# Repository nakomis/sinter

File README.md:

# Sinter — Combining hardware in cruel and unusual ways

## Support

If you find this useful, please consider buying me a coffee:

## Table of Contents

<!-- toc -->

- [Overview](#overview)
- [Architecture Diagram](#architecture-diagram)
- [Repository Layout](#repository-layout)
- [GA-M68MT-S2 Board Architecture](#ga-m68mt-s2-board-architecture)
- [Hardware](#hardware)
- [Architecture Diagrams](#architecture-diagrams)
- [Support](#support)

<!-- tocstop -->

## Overview

Sinter is an agentic compute rig built around a Phenom II X4 965 (AM3) as the execution engine, a Tang Primer 20K FPGA as the memory and bus bridge, and an ESP32 as the orchestration layer.

The ESP32 accepts natural-language problem descriptions, sends them to a local LLM (via Ollama), receives Forth code in response, compiles it to x86-64, injects the binary into the Phenom II's DDR3 via the FPGA/PCIe bridge, executes it, validates the result, and iterates on failure.

> ⭐⭐⭐⭐⭐ — *"Delightfully unhinged in exactly the right way"* — [Copilot](docs/notes/research/sinter-project-assessment-copilot.md)
>
> ⭐⭐⭐⭐⭐ — *"Slow, uncached, synchronization hell"* — [ChatGPT](docs/notes/research/sinter-project-assessment-chatgpt.md#direct-execution-from-bar)
>
> ⭐⭐⭐⭐⭐ — *"Ambitious and cool, but genuinely tricky"* — [Grok](docs/notes/research/sinter-project-assessment-grok.md#3-pci-bar-execute-in-place-architecture--high-risk-many-pitfalls)
>
> ⭐⭐⭐⭐⭐ — *"A desk of whirring salvage spending three days to say 'Hello'"* — Claude

## Architecture Diagram

## Repository Layout

```
sinter/
  embedded/
    esp32/      # ESP32 firmware: agentic loop, Forth-to-x86-64 compiler, orchestration
    fpga/       # HDL for Tang Primer 20K: DDR3 bridge, PCIe endpoint, SATA controller
    phenom/     # Bare-metal x86: bootloader, kernel modules, MSR tooling
  forth/        # Forth-to-x86-64 compiler: portable C11 library, host tests (SINT-25)
  docs/
    architecture/   # draw.io source and generated SVGs
```

## GA-M68MT-S2 Board Architecture

For reference, the textbook early-2000s Intel desktop block diagram looks like
this:

CPU on a front-side bus to a **northbridge** (MCH) that owns RAM and AGP/PCIe×16,
then a **southbridge** (ICH) hanging off it that fans out to PCI, USB, SATA/IDE,
audio, LAN, Super I/O (PS/2, serial, parallel, floppy) and the BIOS flash. Fast
stuff close to the CPU, slow/legacy stuff one hop further out.

The Sinter host board (Gigabyte GA-M68MT-S2, Phenom II AM3, nForce 630a /
GeForce 7025) is **not** that picture. It differs in three important ways:

1. **RAM doesn't go through the chipset.** AM3 CPUs have the DDR3 memory
   controller **on-die**. The DIMM slots connect straight to the CPU.
2. **No FSB — it's HyperTransport.** The CPU↔chipset link is a HyperTransport
   3.0 point-to-point bus.
3. **No separate north/southbridge — it's one chip.** The nForce 630a / MCP68
   is a single-chip chipset: PCIe root, the integrated GeForce 7025 iGPU (the
   VGA output), PCI, USB, SATA, LAN MAC, HD Audio, LPC and the SPI master all
   in one package.

Two project-specific extras the generic diagram doesn't show:

- **BIOS is SPI, not LPC.** The MX25L1605E talks SPI to the chipset's SPI
  master — which is why a serprog rig works at all.
- **DualBIOS.** There are **two** flash chips on that SPI bus plus a small
  selector (the "DualBIOS controller").

## Hardware

| Component | Role |
|---|---|
| Phenom II X4 965 (AM3 / GA-M68MT-S2) | x86-64 execution engine |
| Tang Primer 20K FPGA + DDR3 SO-DIMM | Memory bridge, PCIe endpoint, SATA/SPI controller |
| ESP32 | Orchestration, Forth compiler, Ollama client |
| ESP32-S3-CAM | Vision input for inference tasks |

## Architecture Diagrams

`docs/architecture/sinter.drawio` is the source for the diagram above.
The SVG is auto-regenerated on commit by the pre-commit hook in `.githooks/pre-commit`.

To activate the hook after cloning:

```bash
git config core.hooksPath .githooks
```

## Support

If you find this useful, please consider buying me a coffee:

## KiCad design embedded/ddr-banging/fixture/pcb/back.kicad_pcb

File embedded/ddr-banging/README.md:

# DDR-banging (SINT-100)

Driving a desktop DDR3 DIMM directly from an RP2350B, so that an ESP32 can have
gigabytes of RAM. Plane epic: **SINT-100**.

| Path | What |
|---|---|
| `RUNBOOK.md` | Bring-up, step by step: parcel to first burst, with what "good" looks like at each step |
| `EXECUTOR.md` | Design note for the PIO executor (milestone 11): SM layout, word streams, timing, draft programs |
| `firmware/` | RP2350B bring-up firmware: shell, DLL-off DDR3 sequences, ESP32 link (slave) |
| `proto/` | `ddrlink`: the ESP32 ↔ RP2350B SPI protocol, shared by both sides |
| `esp32-client/` | ESP-IDF component `ddrbang` (the ESP32's API to the DIMM) and the 128 MB write/verify test |
| `pogo-pins.md` | Which DIMM pads the fixture contacts, and what each carries |
| `fixture/dimm-pogo-fixture.scad` | Resin pogo-pin fixture (Elegoo Mars 5 Ultra): two jaws, floor, end stops, notch key, hole test strip, insertion gauge |
| `fixture/pcb/gen_pcb.py` | Generates the two breakout PCBs (KiCad) from the `.scad`'s numbers |
| `fixture/pcb/art/` | Silkscreen cats: Tau (front board), Kappa (back board) |

## Rebuilding

```sh
# STLs
openscad -D 'part="front"' -o fixture/stl/front.stl fixture/dimm-pogo-fixture.scad   # also back | test | gauge

# PCBs, DRC, Gerbers for JLCPCB
cd fixture/pcb
python3 gen_pcb.py
kicad-cli pcb drc front.kicad_pcb        # and back
kicad-cli pcb export gerbers --layers F.Cu,B.Cu,F.Mask,B.Mask,F.SilkS,B.SilkS,Edge.Cuts --no-x2 --subtract-soldermask -o gerbers-front/ front.kicad_pcb
kicad-cli pcb export drill --format excellon --excellon-separate-th -o gerbers-front/ front.kicad_pcb
```

Change geometry in the `.scad` only; the PCB generator parses pin lists, pad
positions and bolt positions from it, so the jaw and the boards cannot disagree.

## Key numbers

- Test stick: Samsung M391B5673FH0-CH9 (2 GB 2Rx8 ECC UDIMM, K4B1G0846F chips).
- Gold fingers 2.4 mm tall (measured); pin rows at 0.75 and 2.03 mm above the edge.
- P75-B1 pogo pins; 1.15 mm plated holes (JLCPCB PTH tolerance +0.13/−0.08).
- Four M3×25 bolts clamp PCB–jaw–floor–jaw–PCB.
- PCBs ordered from JLCPCB 2026-10-10: 1.6 mm, front black, back white.

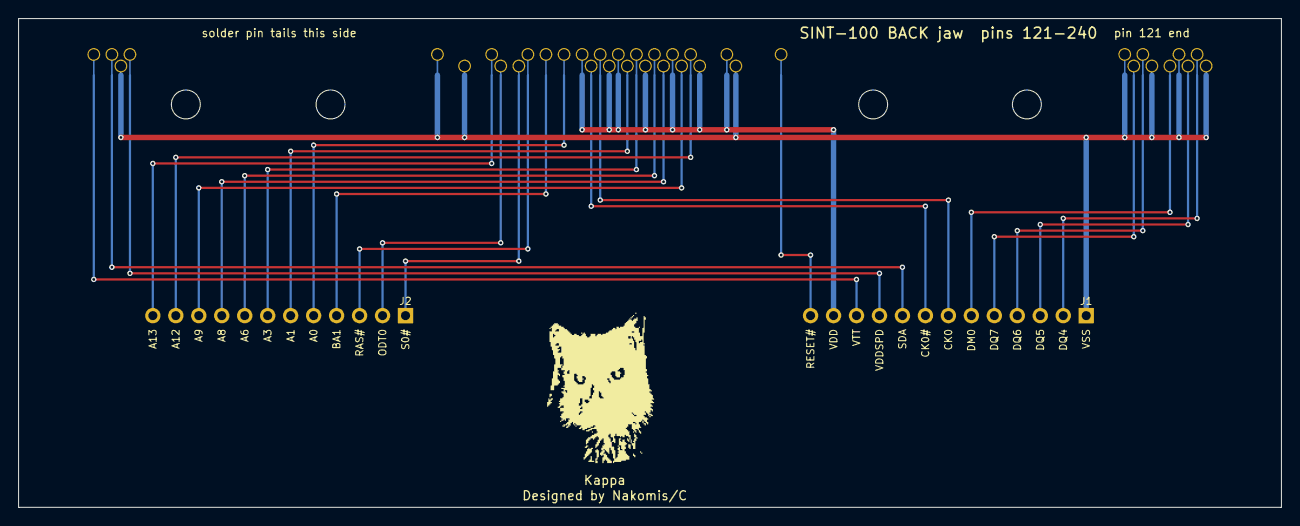
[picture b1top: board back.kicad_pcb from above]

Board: 2 copper layers, 139.7 x 54.0 mm, 45 parts (0 on the bottom side), 25 nets.

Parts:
ART2: Kappa; ART_KAPPA
H1, H2, H3, H4: M3
J1: HDR_1x13
J2: HDR_1x12
P121, P124, P127, P130, P169, P199, P202, P237: VSS; POGO_P75
P122: DQ4; POGO_P75
P123: DQ5; POGO_P75
P125: DM0; POGO_P75
P128: DQ6; POGO_P75
P129: DQ7; POGO_P75
P168: RESET#; POGO_P75
P170, P173, P176, P179, P182, P183, P186: VDD; POGO_P75
P174: A12; POGO_P75
P175: A9; POGO_P75
P177: A8; POGO_P75
P178: A6; POGO_P75
P180: A3; POGO_P75
P181: A1; POGO_P75
P184: CK0; POGO_P75
P185: CK0#; POGO_P75
P188: A0; POGO_P75
P190: BA1; POGO_P75
P192: RAS#; POGO_P75
P193: S0#; POGO_P75
P195: ODT0; POGO_P75
P196: A13; POGO_P75
P236: VDDSPD; POGO_P75
P238: SDA; POGO_P75
P240: VTT; POGO_P75

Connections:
A0: J2.5, P188.1
A1: J2.6, P181.1
A3: J2.7, P180.1
A6: J2.8, P178.1
A8: J2.9, P177.1
A9: J2.10, P175.1
A12: J2.11, P174.1
A13: J2.12, P196.1
BA1: J2.4, P190.1
CK0: J1.7, P184.1
CK0#: J1.8, P185.1
DM0: J1.6, P125.1
DQ4: J1.2, P122.1
DQ5: J1.3, P123.1
DQ6: J1.4, P128.1
DQ7: J1.5, P129.1
ODT0: J2.2, P195.1
RAS#: J2.3, P192.1
RESET#: J1.13, P168.1
S0#: J2.1, P193.1
SDA: J1.9, P238.1
VDD: J1.12, P170.1, P173.1, P176.1, P179.1, P182.1, P183.1, P186.1
VDDSPD: J1.10, P236.1
VSS: J1.1, P121.1, P124.1, P127.1, P130.1, P169.1, P199.1, P202.1, P237.1
VTT: J1.11, P240.1

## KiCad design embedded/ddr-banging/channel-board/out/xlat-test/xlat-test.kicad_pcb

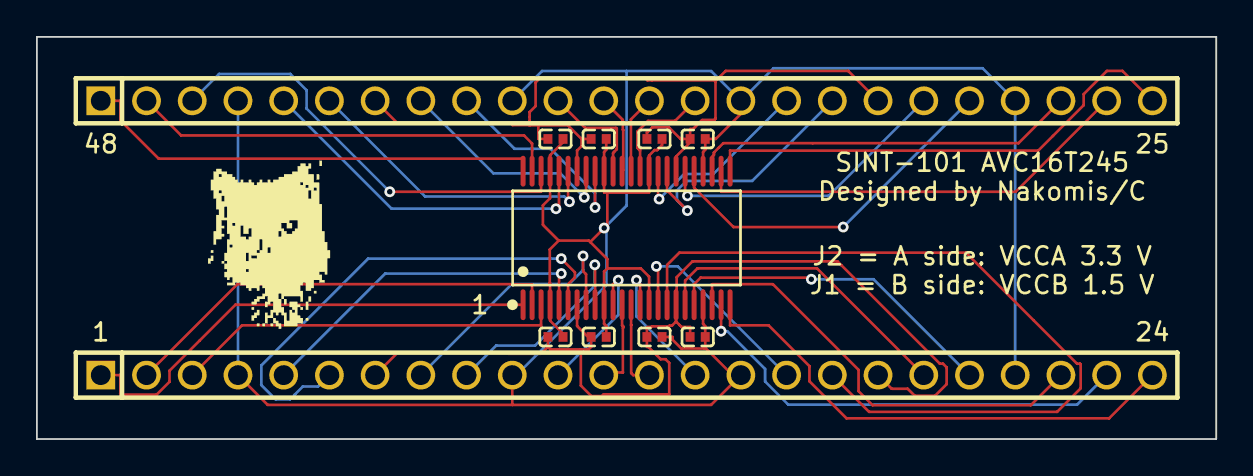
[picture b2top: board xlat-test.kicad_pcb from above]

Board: 2 copper layers, 65.5 x 22.3 mm, 12 parts (0 on the bottom side), 39 nets.

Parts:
ART: ART
C1, C3, C5, C7: 100nF; C0402
C2, C4, C6, C8: 1uF; C0402
J1, J2: 1x24 header; HDR-TH_24P-P2.54-V-M
U1: SN74AVC16T245DGGR; TSSOP-48_L12.6-W6.2-P0.50-LS8.1-BL

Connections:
1A1: J2.2, U1.47
1A2: J2.3, U1.46
1A3: J2.5, U1.44
1A4: J2.6, U1.43
1A5: J2.8, U1.41
1A6: J2.9, U1.40
1A7: J2.11, U1.38
1A8: J2.12, U1.37
1B1: J1.2, U1.2
1B2: J1.3, U1.3
1B3: J1.5, U1.5
1B4: J1.6, U1.6
1B5: J1.8, U1.8
1B6: J1.9, U1.9
1B7: J1.11, U1.11
1B8: J1.12, U1.12
1DIR: J1.1, U1.1
1OE#: J2.1, U1.48
2A1: J2.13, U1.36
2A2: J2.14, U1.35
2A3: J2.16, U1.33
2A4: J2.17, U1.32
2A5: J2.19, U1.30
2A6: J2.20, U1.29
2A7: J2.22, U1.27
2A8: J2.23, U1.26
2B1: J1.13, U1.13
2B2: J1.14, U1.14
2B3: J1.16, U1.16
2B4: J1.17, U1.17
2B5: J1.19, U1.19
2B6: J1.20, U1.20
2B7: J1.22, U1.22
2B8: J1.23, U1.23
2DIR: J1.24, U1.24
2OE#: J2.24, U1.25
GND: C1.2, C2.2, C3.2, C4.2, C5.2, C6.2, C7.2, C8.2, J1.4, J1.10, J1.15, J1.21, J2.4, J2.10, J2.15, J2.21, U1.4, U1.10, U1.15, U1.21, U1.28, U1.34, U1.39, U1.45
VCCA: C1.1, C2.1, C3.1, C4.1, J2.7, J2.18, U1.31, U1.42
VCCB: C5.1, C6.1, C7.1, C8.1, J1.7, J1.18, U1.7, U1.18

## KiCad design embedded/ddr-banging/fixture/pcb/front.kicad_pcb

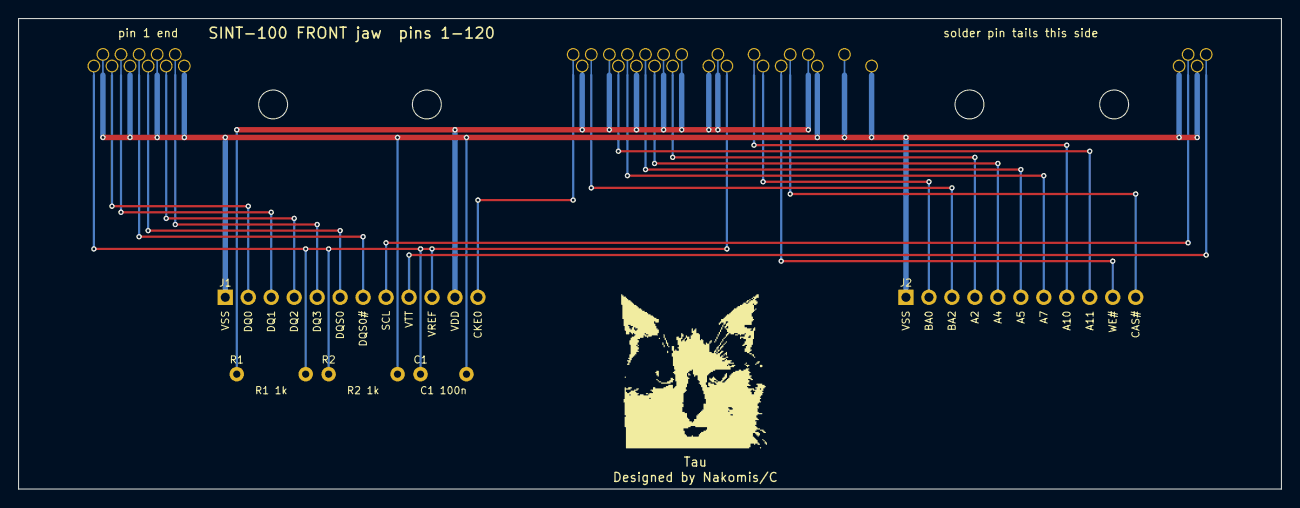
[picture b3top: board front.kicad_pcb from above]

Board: 2 copper layers, 139.7 x 52.0 mm, 48 parts (0 on the bottom side), 22 nets.

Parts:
ART1: Tau; ART_TAU
C1: 100n; CAP_THT
H1, H2, H3, H4: M3
J1: HDR_1x12
J2: HDR_1x11
P1, P67: VREF; POGO_P75
P2, P5, P8, P11, P77, P80, P83, P117, P119: VSS; POGO_P75
P3: DQ0; POGO_P75
P4: DQ1; POGO_P75
P6: DQS0#; POGO_P75
P7: DQS0; POGO_P75
P9: DQ2; POGO_P75
P10: DQ3; POGO_P75
P50: CKE0; POGO_P75
P51, P54, P57, P60, P62, P65, P66, P76: VDD; POGO_P75
P52: BA2; POGO_P75
P55: A11; POGO_P75
P56: A7; POGO_P75
P58: A5; POGO_P75
P59: A4; POGO_P75
P61: A2; POGO_P75
P70: A10; POGO_P75
P71: BA0; POGO_P75
P73: WE#; POGO_P75
P74: CAS#; POGO_P75
P118: SCL; POGO_P75
P120: VTT; POGO_P75
R1, R2: 1k; AXIAL

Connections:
A2: J2.4, P61.1
A4: J2.5, P59.1
A5: J2.6, P58.1
A7: J2.7, P56.1
A10: J2.8, P70.1
A11: J2.9, P55.1
BA0: J2.2, P71.1
BA2: J2.3, P52.1
CAS#: J2.11, P74.1
CKE0: J1.12, P50.1
DQ0: J1.2, P3.1
DQ1: J1.3, P4.1
DQ2: J1.4, P9.1
DQ3: J1.5, P10.1
DQS0: J1.6, P7.1
DQS0#: J1.7, P6.1
SCL: J1.8, P118.1
VDD: J1.11, P51.1, P54.1, P57.1, P60.1, P62.1, P65.1, P66.1, P76.1, R1.1
VREF: C1.1, J1.10, P1.1, P67.1, R1.2, R2.1
VSS: C1.2, J1.1, J2.1, P2.1, P5.1, P8.1, P11.1, P77.1, P80.1, P83.1, P117.1, P119.1, R2.2
VTT: J1.9, P120.1
WE#: J2.10, P73.1

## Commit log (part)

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2026-05-03 chore: scaffold sinter with standard project layout
2026-05-03 chore(docs): replace corrupt icons with re-exported versions from Draw Things
2026-05-20 docs: add GA-M68MT-S2 board architecture mermaid diagram
    Captures the three ways the AM3/nForce 630a board differs from the
    generic early-2000s Intel block diagram: on-die DDR3 IMC, HyperTransport
    to chipset, and a single-chip MCP68 (no separate north/southbridge).
    Also shows the DualBIOS pair on the SPI bus behind the selector.
2026-05-20 docs: add reference Intel block diagram from Wikimedia, expand blurb
    Includes the textbook early-2000s Intel motherboard diagram (Moxfyre,
    Wikimedia Commons, CC BY-SA 3.0) as the reference picture, then walks
    through the three ways the AM3/nForce 630a board diverges from it, plus
    the SPI-not-LPC and DualBIOS specifics relevant to SINT-34/39.
2026-05-20 docs: vendor motherboard block diagram locally
    Wikimedia's upload.wikimedia.org hot-link returned a 'file not found'
    in GitHub's image proxy (the path Wikimedia exposed wasn't the one
    hosting the original). Copy the SVG into docs/ instead, keeping the
    'courtesy of Moxfyre, Wikimedia Commons — CC BY-SA 3.0' attribution
    in the README.
2026-05-20 docs: redraw reference block diagram in draw.io
    Replaces the vendored CC BY-SA 3.0 Wikimedia SVG with a hand-drawn
    equivalent under docs/architecture/, so the whole repo stays cleanly
    CC0. Same content: CPU on FSB to northbridge (with RAM and AGP/PCIe
    x16), northbridge to southbridge over the hub link, southbridge fanning
    out to PCI / USB / SATA-IDE / HD Audio / LAN / Super I/O / BIOS flash.
    Source: docs/architecture/motherboard-block-diagram.drawio
2026-05-20 docs: redraw GA-M68MT-S2 block diagram in draw.io
    Replaces the inline mermaid flowchart with a draw.io diagram styled to
    match the generic Intel reference diagram added in the same PR — same
    colour palette (blue CPU, green chipset/bridge nodes, yellow direct-attached,
    red peripheral leaves) so the two sit side-by-side and the structural
    differences (DIMMs on the CPU, HyperTransport not FSB, single chipset,
    DualBIOS pair on SPI) are visually obvious.
2026-05-20 docs: draft target architecture diagram
    The README already references docs/architecture/sinter.svg as 'the
    architecture diagram', but the file didn't exist yet. This is a first
    pass at it, drawn in the same style as the two block diagrams (blue
    compute / green fabric / yellow memory / red I/O-or-leaf).
    Captures the full agentic loop:
    pseudocode + vision input
2026-05-20 docs: notes on executing code directly from FPGA PCI BAR
    Design notes for the SINT execution path (ESP32 -> SPI -> FPGA -> DDR3
    -> PCI BAR -> Phenom II executes). Captures the bits worth keeping
    from a Gemini design discussion, plus a couple of points it got wrong:
    - Cache coherency: BAR must be marked Uncacheable via MTRR or PAT, or
    the Phenom's L1i will happily keep executing stale code while the
    ESP32 rewrites the FPGA DDR3 underneath. This is the single
2026-05-20 docs: expand BAR/DualBIOS notes; add research transcripts
    Folded in the cross-referenced bits from ChatGPT and Grok assessments,
    keeping only what all three of us independently agreed on or that has a
    specific defensible source. Discarded the ATX-standby trick, the Award
    checksum 'DualBIOS bypass' framing, and the invd-as-SMC-safeguard
    suggestion - each flagged in dualbios-strategy.md §6 with the reason.
    pci-bar-execute.md additions:
2026-05-20 docs: fold in Copilot's unique nuggets; add transcript
    Microsoft Copilot's assessment is the most sober of the four LLM
    responses to the Sinter project preamble (alongside ChatGPT, Grok, and
    my own running notes). No invented IDs, no ATX-standby trick, no invd,
    no mythical DIP switches. Three genuinely-new useful points folded in:
    pci-bar-execute.md:
    - UD2 (0F 0B) padding at the tail of the BAR code region as a guard
2026-05-20 docs(research): save Copilot follow-up; not folded yet
    Detailed memory map + MTRR/PAT + handshake sketch from Copilot. Saved
    to research/ but explicitly NOT folded into the distilled notes,
    because it is paper architecture written before we have:
    - a verified BIOS dump (SINT-34 still blocking),
    - lspci -vv output from the real board,
    - the Tang Primer 20K with a working PCI target IP claiming a BAR.
2026-05-20 docs(research): save Copilot follow-up 2 (failures/MSRs/fences)
    Three artefacts in one paste: a 15-entry failure-mode catalogue, an
    AMD K10 MSR cheat-sheet, and a comparison table of x86 cache/ordering
    primitives. Saved verbatim for traceability.
    NOT folded into the distilled notes. Two reasons captured in the
    file's preamble:
    1. The worked MTRR example in section 2.8 contains arithmetic errors.
2026-05-20 docs(research): reframe corrections as 'disputed; needs verification'
    The original preamble said 'Copilot got these MSR values wrong, here
    are the right ones'. That framing was itself overconfident: every
    'correction' is produced by the same kind of LLM that produced the
    original answer, and 'looks plausible' is not evidence of correctness
    in either direction.
    Reframed:
2026-05-20 docs: capture process takeaways - multi-LLM + verify-against-silicon
    Closing artefacts for PR #4. Two short companion files capturing the
    two main process lessons from the SINT-34/SINT-39 design phase.
    multi-llm-consultation.md:
    - Why bouncing the same numbered questions off four free-tier LLMs
    in parallel catches errors that single-model consultation does not
    (Gemini's DualBIOS hardware checksum invention, Grok's invd
2026-05-20 docs(dualbios): document flashrom -p internal as no-soldering dump path
    Add §2a covering the Linux live USB / internal programmer path for the
    currently-active chip (M_BIOS on a normal boot), and reframe the existing
    clip/desolder material as §2b — the fallback for B_BIOS, unbootable boards,
    and all writes. New §5a explains why internal flashrom is not the right
    tool for SINT-39 writes (chipset WP lockdown, DualBIOS interference).
2026-05-20 docs(pci-bar-execute): fold Cabal MCP first-run findings
    New §10 captures the cross-LLM consultation from the freshly-merged
    cabal-mcp. Three takeaways worth folding in: the bootstrap dependency
    (Gemini's catch — x86 reset vector goes to BIOS, not the BAR), W^X
    discipline as the safe write-then-flip pattern, and a frank note that
    the prompt itself was misframed (I asked about PCIe x1 Gen1 when the
    design uses legacy PCI 32/33). Verbatim transcripts saved under
2026-05-22 docs(readme): add LLM review pull-quotes to the Sinter README
2026-05-22 docs(readme): move review block into Overview, gold stars, populate TOC
2026-05-22 docs(readme): retitle, regenerate TOC, add TOC generation to pre-commit hook
2026-05-22 docs(readme): move review block below the Overview paragraphs
2026-05-22 docs(readme): link AI review quotes to their research notes
2026-06-11 docs(notes): PCI 5V signalling risk, Forth compiler design, Linux-first bring-up (SINT-93/94/95)
    - pci-bar-execute.md: new §6a — desktop PCI slots are 5V-signalling, the
    GW2A's LVCMOS33 I/O is not 5V tolerant; verify slot keying/VI/O and add
    quickswitch bus switches before the card goes anywhere near the slot
    - pci-bar-execute.md: recommend porting an open-source PCI 32/33 target
    core (pci32tlite) rather than scratch-building (§7, SINT-94)
    - pci-bar-execute.md: clarify SINT-34 gates SINT-39 only, not the PCI
